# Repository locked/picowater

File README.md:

cd build

cmake -DPICO_BOARD=pico_w -DWIFI_SSID="<wifi>" -DWIFI_PASSWORD="<secret>" -DSERVER_IP="<ip>" -DSERVER_PORT=<port> ..

make

# Sources

https://github.com/iiot2k/pico-lib2/blob/main/src/dev/dev_ds3231/dev_ds3231.c

https://ghubcoder.github.io/posts/awaking-the-pico/

https://github.com/ghubcoder/PicoSleepRtc/blob/master/ds3232rtc.cpp

https://github.com/raspberrypi/pico-examples/blob/master/adc/hello_adc/hello_adc.c

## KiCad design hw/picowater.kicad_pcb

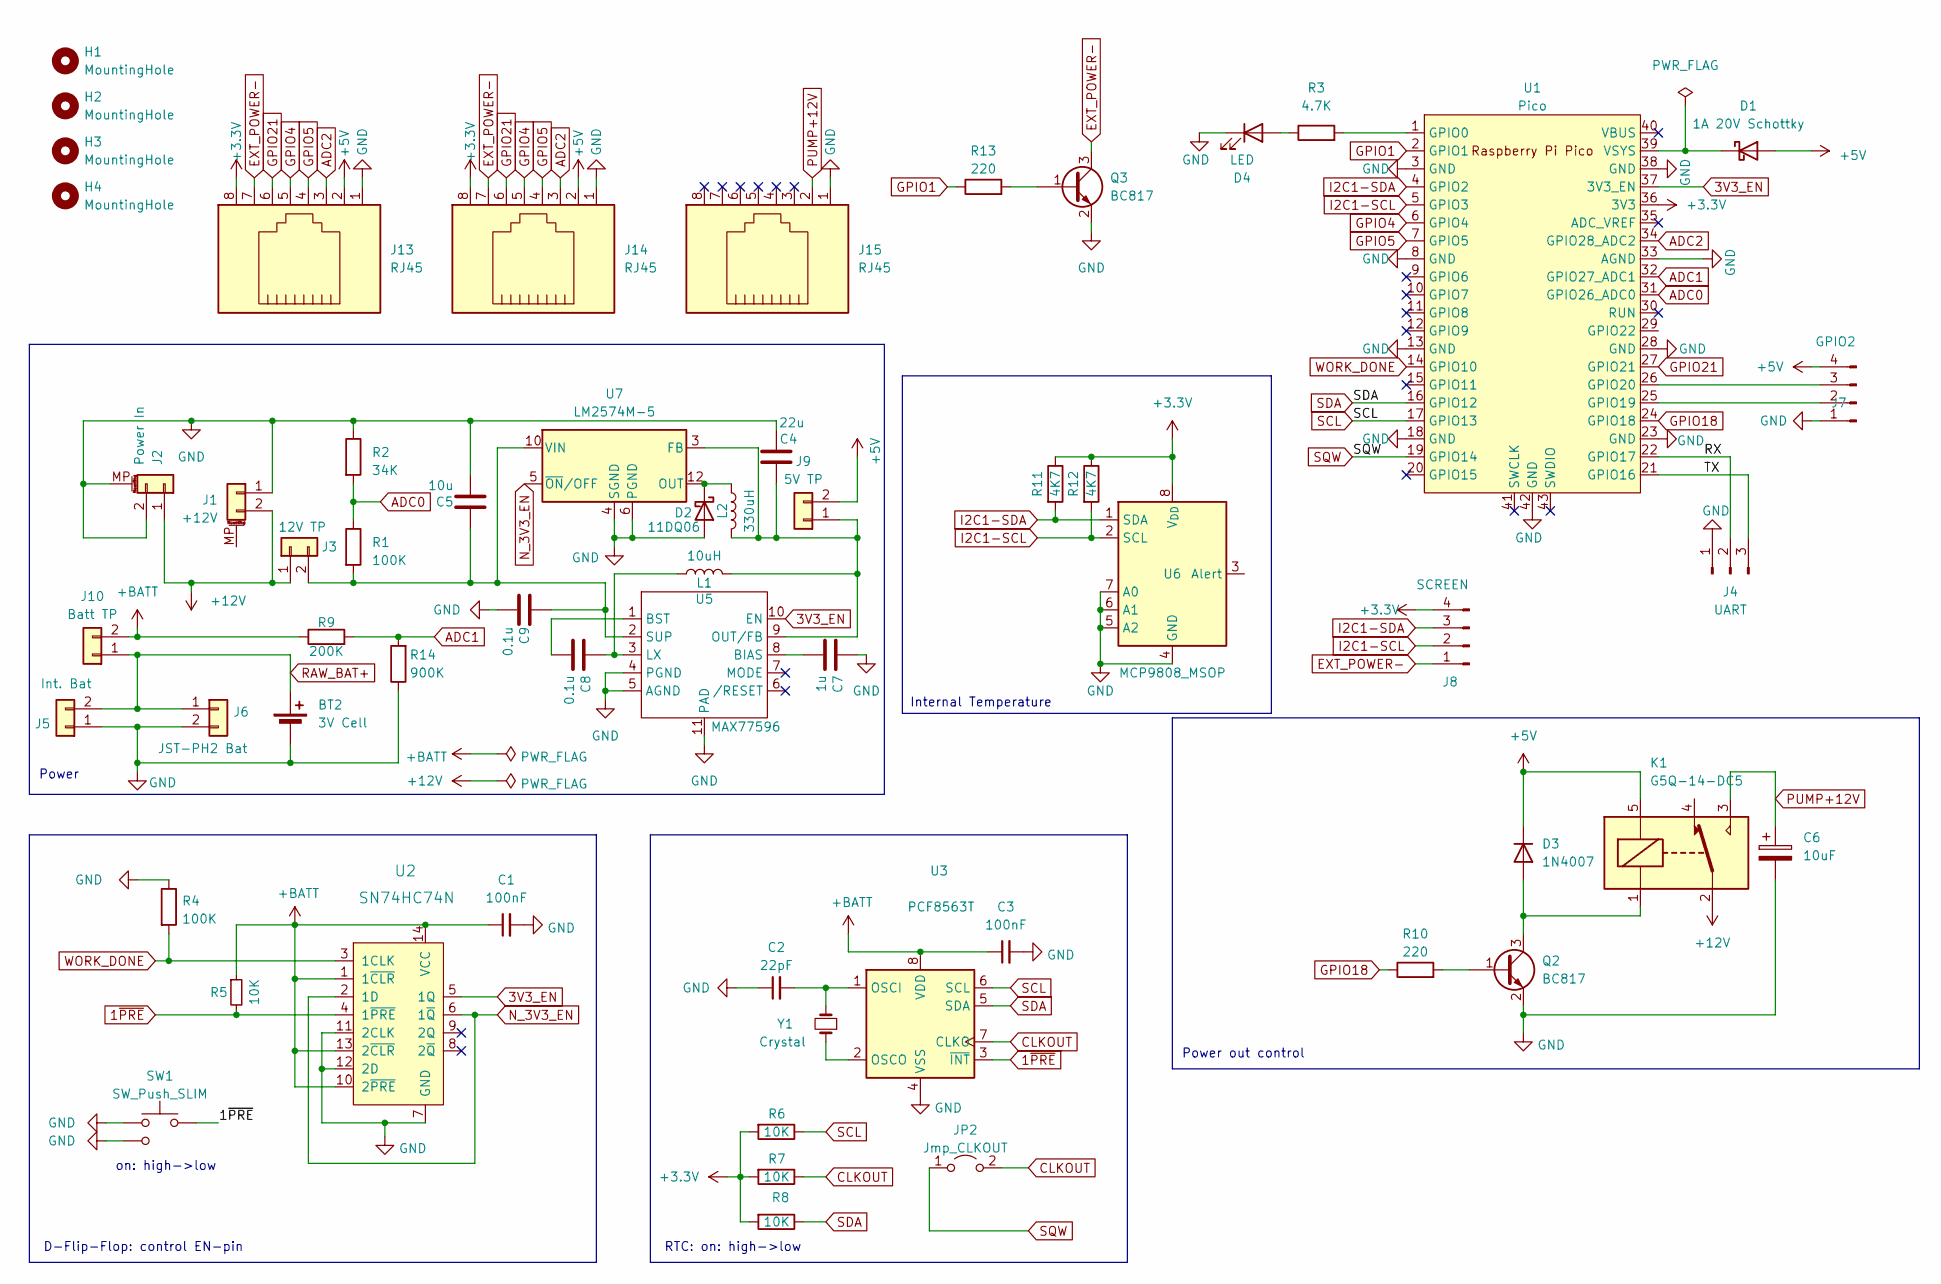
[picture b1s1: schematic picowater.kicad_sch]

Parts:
BT2: 3V Cell; MPD_BC501SM-TR_custom
C1, C3: 100nF; C_0402_1005Metric; LCSC C1525
C2: 22pF; C_0402_1005Metric; LCSC C1555
C4: 22u; C_0805_2012Metric; LCSC C2846677
C5: 10u; C_0805_2012Metric; LCSC C2846677
C6: 10uF; CP_Radial_D8.0mm_P3.80mm
C7: 1u; C_0603_1608Metric
C8, C9: 0.1u; C_0603_1608Metric
D1: 1A 20V Schottky; D_SOD-123F; LCSC C169527
D2: 11DQ06
D3: 1N4007; D_SOD-123; LCSC C3018540
D4: LED; LED_0603_1608Metric_Pad1.05x0.95mm_HandSolder; JLCPCB Part Number C72041
H1, H2, H3, H4: MountingHole; hole_5mm
J1: +12V; PinSocket_1x02_P2.54mm_Vertical
J2: Power In; BarrelJack_CUI_PJ-102AH_Horizontal
J3: 12V TP; PinHeader_1x02_P2.54mm_Vertical
J4: UART; PinHeader_1x03_P2.54mm_Vertical
J5: Int. Bat; PinHeader_1x02_P2.54mm_Vertical; LCSC C295747
J6: JST-PH2 Bat; JST_PH_S2B-PH-SM4-TB_1x02-1MP_P2.00mm_Horizontal; LCSC C295747
J7: GPIO2; PinHeader_1x04_P2.54mm_Vertical
J8: SCREEN; PinHeader_1x04_P2.54mm_Vertical
J9: 5V TP; PinHeader_1x02_P2.54mm_Vertical
J10: Batt TP; PinHeader_1x02_P2.54mm_Vertical
J13, J14, J15: RJ45; RJ45_BEL_SS74301-00x_Vertical
JP2: Jmp_CLKOUT; SolderJumper-2_P1.3mm_Open_Pad1.0x1.5mm
K1: G5Q-14-DC5; Relay_SPDT_Omron-G5Q-1
L1: 10uH; C_0805_2012Metric
L2: 330uH
Q2, Q3: BC817; SOT-23
R1, R4: 100K; R_0402_1005Metric; LCSC C25741
R2: 34K; R_0402_1005Metric; LCSC C48939
R3: 4.7K; R_0402_1005Metric
R5, R6, R8: 10K; R_0402_1005Metric; LCSC C25744
R7: 10K; R_0805_2012Metric; LCSC C25744
R9: 200K; R_0402_1005Metric
R10, R13: 220; R_0402_1005Metric; LCSC C2909336
R11, R12: 4K7; C_0603_1608Metric; LCSC C25900
R14: 900K; R_0402_1005Metric
SW1: SW_Push_SLIM; SW_Tactile_SPST_Angled_PTS645Vx31-2LFS
U1: Pico; RPi_Pico_SMD_TH
U2: SN74HC74N; SO-14_5.3x10.2mm_P1.27mm; MPN SN74HC74N; Digi-Key_PN 296-1602-5-ND
U3: PCF8563T; SOIC-8_3.9x4.9mm_P1.27mm; LCSC C7440
U5: MAX77596; TDFN-10-EP_2.5mm
U6: MCP9808_MSOP; MSOP-8_3x3mm_P0.65mm; LCSC C129490
U7: LM2574M-5
Y1: Crystal; Crystal_SMD_3215-2Pin_3.2x1.5mm; LCSC C32346

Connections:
1~PRE: R5.2, SW1.2, U2.4 (1~PRE), U3.3 (~INT)
3V3_EN: U1.37 (3V3_EN), U2.5 (1Q), U5.10 (EN)
+3.3V: J8.4, J13.8, J14.8, R6.2, R7.2, R8.2, R11.1, R12.1, U1.36 (3V3), U6.8 (V_{DD})
+5V: D1.2 (A), D3.1 (K), J7.4, J9.2, J13.2, J14.2, K1.5
+12V: J1.2, J2.1, J3.1, K1.2
+BATT: C1.1, C3.1, J10.2, R5.1, R9.1, U2.1 (1~CLR), U2.10 (2~PRE), U2.13 (2~CLR), U2.14 (VCC), U3.8 (VDD)
/RX: J4.2, U1.22 (GPIO17)
/TX: J4.3, U1.21 (GPIO16)
ADC0: R1.1, R2.2, U1.31 (GPIO26_ADC0)
ADC1: R9.2, R14.2, U1.32 (GPIO27_ADC1)
ADC2: J13.3, J14.3, U1.34 (GPIO28_ADC2)
CLKOUT: JP2.2 (B), R7.1, U3.7 (CLKO)
EXT_POWER-: J8.1, J13.7, J14.7, Q3.3 (C)
GND: BT2.2 (-), C1.2, C2.1, C3.2, C4.2, C5.2, C6.2, C7.1, C9.2, D2.2 (A), D4.1 (K), J1.1, J2.2, J2.MP (MountPin), J4.1, J5.1, J6.2, J7.1, J13.1, J14.1, J15.1, Q2.2 (E), Q3.2 (E), R2.1, R4.1, R14.1, SW1.1, SW1.3 (1), U1.3 (GND), U1.8 (GND), U1.13 (GND), U1.18 (GND), U1.23 (GND), U1.28 (GND), U1.33 (AGND), U1.38 (GND), U1.42 (GND), U2.7 (GND), U2.11 (2CLK), U2.12 (2D), U3.4 (VSS), U5.4 (PGND), U5.5 (AGND), U5.11 (PAD), U6.4 (GND), U6.5 (A2), U6.6 (A1), U6.7 (A0), U7.4 (SGND), U7.6 (PGND)
GPIO1: R13.1, U1.2 (GPIO1)
GPIO4: J13.5, J14.5, U1.6 (GPIO4)
GPIO5: J13.4, J14.4, U1.7 (GPIO5)
GPIO18: R10.1, U1.24 (GPIO18)
GPIO21: J13.6, J14.6, U1.27 (GPIO21)
I2C1-SCL: J8.2, R12.2, U1.5 (GPIO3), U6.2 (SCL)
I2C1-SDA: J8.3, R11.2, U1.4 (GPIO2), U6.1 (SDA)
N_3V3_EN: U2.2 (1D), U2.6 (1~Q), U7.5 (~ON/OFF)
unnamed: D1.1 (K), U1.39 (VSYS)
unnamed: D2.1 (K), L2.1, U7.12 (OUT)
unnamed: D3.2 (A), K1.1, Q2.3 (C)
unnamed: D4.2 (A), R3.1
unnamed: C5.1, C9.1, J3.2, R1.2, U5.2 (SUP), U7.10 (VIN)
unnamed: J7.2, U1.25 (GPIO19)
unnamed: J7.3, U1.26 (GPIO20)
unnamed: C4.1, J9.1, L1.2, L2.2, U5.9 (OUT/FB), U7.3 (FB)
unnamed: Q2.1 (B), R10.2
unnamed: Q3.1 (B), R13.2
unnamed: R3.2, U1.1 (GPIO0)
unnamed: C2.2, U3.1 (OSCI), Y1.2
unnamed: U3.2 (OSCO), Y1.1
unnamed: C7.2, U5.8 (BIAS)
unnamed: C8.2, U5.1 (BST)
unnamed: C8.1, L1.1, U5.3 (LX)
PUMP+12V: C6.1, J15.2, K1.3
RAW_BAT+: BT2.1 (+), J5.2, J6.1, J10.1
SCL: R6.1, U1.17 (GPIO13), U3.6 (SCL)
SDA: R8.1, U1.16 (GPIO12), U3.5 (SDA)
SQW: JP2.1 (A), U1.19 (GPIO14)
WORK_DONE: R4.2, U1.14 (GPIO10), U2.3 (1CLK)

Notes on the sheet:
Power
on: high->low
Power out control
RTC: on: high->low
D-Flip-Flop: control EN-pin
Internal Temperature

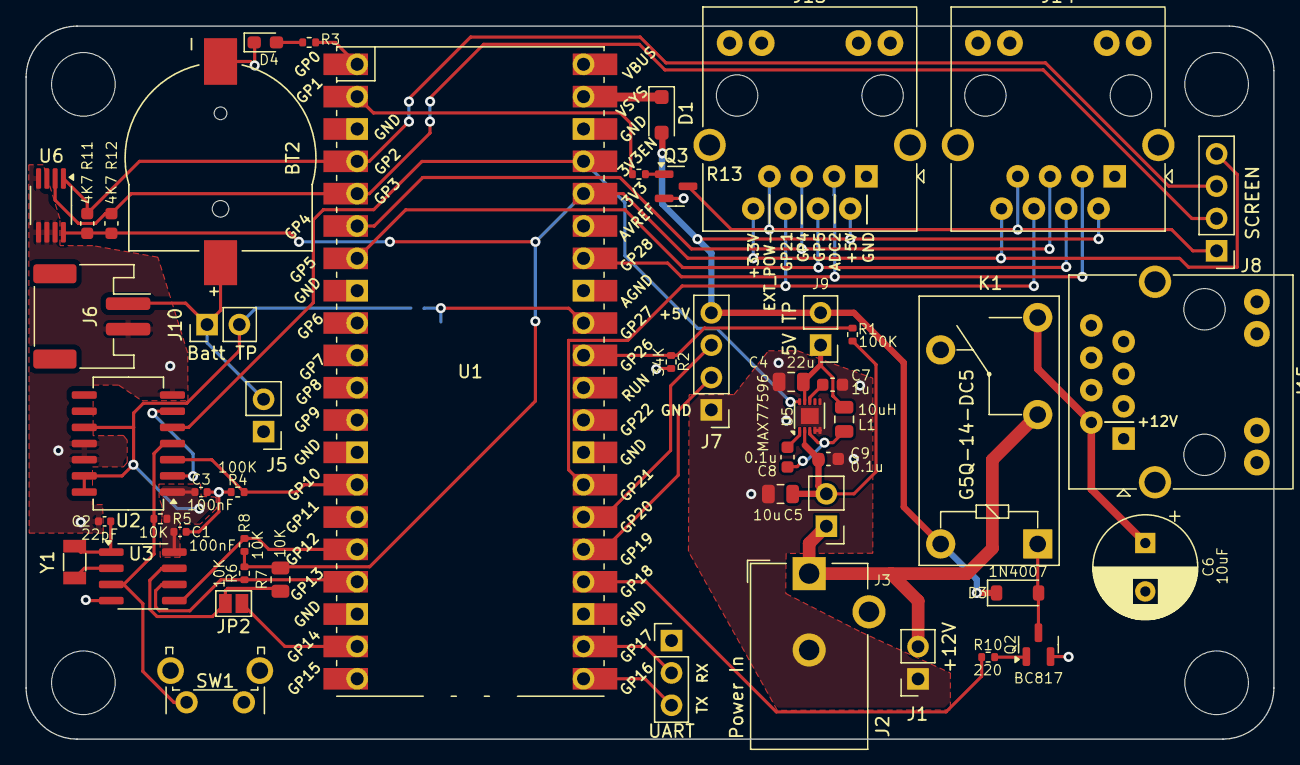
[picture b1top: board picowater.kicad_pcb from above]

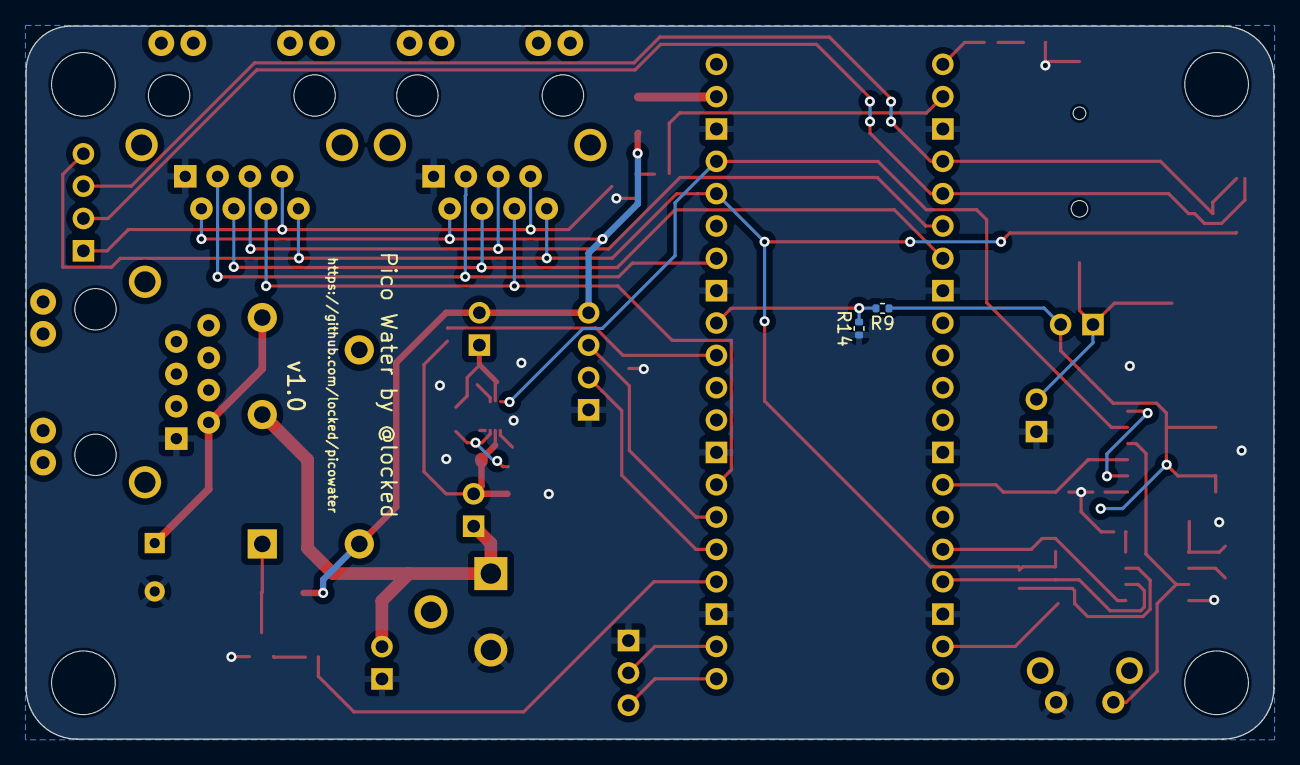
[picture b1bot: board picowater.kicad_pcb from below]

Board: 2 copper layers, 98.0 x 56.0 mm, 56 parts (2 on the bottom side), 43 nets.

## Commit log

2023-05-28 high level schema
2023-05-28 add kicad project
2023-05-28 update resistor
2023-05-29 v0.1
2023-06-03 add pico code (from pico_w example library)
2023-06-03 use lib for wifi + send udp beacon + flash led
2023-06-13 update PCB+code
2023-06-13 pcb update
2023-06-13 add sources
2023-06-14 cleanup, use more uart output
2023-07-07 add infinite loop, start motor every 10 min
2023-07-12 use external RTC for wakeup
2023-07-13 cleanup + working sleep/wifi
2023-07-14 update pcb
2023-07-14 wakeup every hour, cleanup
2023-07-14 move rtc functions into new lib, cleanup
2023-07-29 [hw] update pcb
2023-07-29 handle water distance, humidity and cleanup/fixes
2023-07-29 minor cleanups
2023-07-29 [hw] v0.3 release
2023-08-05 change logic + thresholds for real mode
2023-08-18 support for v0.3 PCB (non backward compatible) + add ssd1306 screen support
2024-03-17 [pcb] new 0.9 release with many changes
    - onboard DC-DC converter
    - onboard RTC
    - onboard Relay circuit
    - new connectors
    - others
2024-04-06 [pcb] fixes following v0.9
2024-04-06 working RTC
2024-04-09 [pcb] fixes
2024-04-09 add datasheets
2024-04-28 better use of the new rtc
2024-04-28 [pcb] add internal temp sensor
2024-04-28 fix humidity ADC
2024-05-01 working sockets (very basic)
2024-05-01 parse date in json to set RTC
2024-05-01 add server side php + fixes
2025-03-29 use http, use simpler lib of rtc, cleanup
2025-03-29 [pcb] lots of fixes and simplification
2025-04-05 [hw] new PCB with RJ45 as connector and other changes + case
2025-04-05 [case] add stl
2025-04-06 [case] add rj45, power jack and led holes
2025-04-10 [case] adjust screw positions, minor tweaks
2025-04-15 fw: send info to server, pcb: many tweaks
2025-05-25 [fw] change/add PINs for latest PCB
2025-05-25 [pcb] update
2025-05-29 [case] fix top cover
2025-05-29 [case] fixes + add internal battery holder
2025-06-08 [pcb] fix ADC + add internal connector for int. bat
2025-06-08 [case] fix screw size
2025-06-11 [case] minor screws adjustment
2025-06-15 [fw] add support for batlvl2, temperature, add failsafe
2025-07-16 add server side basic services
2025-11-23 [pcb] fix diode polarity on relay
2026-04-25 add sleep if no reboot, remove unused var
